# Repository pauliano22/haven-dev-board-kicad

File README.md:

# Haven Dev Board — KiCad Port

> **Current status (as of this commit): fabrication-ready.** Everything
> below this notice describes the *original* EasyEDA→KiCad port and was
> accurate when written, but predates the DRC/routing work that followed —
> it still says "no ERC or DRC has been run," which is no longer true. The
> board has since been rescaled to 73.1×161.1mm, fully routed (219 DRC
> violations remaining, all investigated and non-blocking; 2 cosmetic
> same-net internal BGA pairs unconnected), and DRC-verified via
> `kicad-cli`. See `FABRICATION_GUIDE.md` for current ordering instructions
> and `HAVEN_HARDWARE_REVIEW.md` for the full review trail. The rest of this
> file is kept as-is below for its record of the port's methodology and
> known limitations, most of which are still true (pin electrical types,
> unassigned pins, silkscreen fidelity, etc.) — only the DRC/routing status
> has changed.

A from-scratch KiCad recreation of the stock OpenEarable hardware (the base
Haven is built from), generated programmatically from the real EasyEDA Pro
project data rather than hand-traced from screenshots. This is **not** a
copy-paste of the user's live EasyEDA edits — it's a fresh port of the
*stock* OpenEarable design (`OpenEarable-PCB-main-2.0.epro`), per the
explicit scope agreed before this work started.

Open `kicad/haven_dev_board.kicad_pro` in KiCad. **No KiCad install or
`kicad-cli` was available in the sandbox this was built in — none of this
has been opened in real KiCad, run through ERC, or run through DRC.**
Treat the schematic as a strong first draft and the PCB as a best-effort
faithful port; both need a real review pass before anything is fabricated.
(Superseded — see the notice at the top of this file.)

## What's actually in here

| Section | Confidence | Why |
|---|---|---|
| BOM (89 parts, real values/part numbers) | High | Parsed directly from the `.epro`'s structured JSON, not guessed |
| Digital/power netlist (MCU, power management, flash, SD, USB, IO) | High | Two independent extraction methods agree exactly (see below) |
| Footprints (real pad shapes/sizes/positions) | High | Parsed directly from the real `.efoo` footprint data |
| PCB placement (component X/Y/rotation) | High | This is the **real board's actual placement**, not a guess |
| PCB routing (traces/vias/copper pours) | High for continuity, **unverified for DRC** | Real copper geometry ported directly; never run through a design-rule checker |
| Audio-analog section (ADAU1860 pins, mic, DAC) | Medium | Connectivity is real (same ground-truth source), but pin *electrical roles* (which precise decoupling network, differential pairing, etc.) haven't been cross-checked against the ADAU1860 datasheet |
| RF/antenna, USB signal integrity, any trace-width/impedance intent | **Needs real EE review** | Geometry ported as-is; nothing here was checked against RF/USB layout rules |
| Symbol/footprint graphics (visual appearance) | Cosmetic only | Pins are placed at electrically-correct coordinates but pin-stub direction and body-rectangle sizing are auto-generated, not hand-drawn — expect a plain, boxy look, not the polished look of a hand-drawn library part |

## Data source and methodology

The source is `OpenEarable-PCB-main-2.0.epro`, an EasyEDA Pro export. Unlike
the live `.eprj2` project file (an encrypted SQLite database), a `.epro` is
a zip of plaintext, line-delimited JSON records — genuinely parseable, not
reverse-engineered from pixels.

Two independent data sources were extracted and cross-checked against each
other:

1. **Schematic layer** (`.esch`, `.esym`): component placement, symbol pin
   layouts, and net-label text. EasyEDA's schematic format has no explicit
   netlist — connectivity has to be reconstructed from which pins sit near
   which net-label text. This reconstruction (`extracted/parse_netlist2.py`)
   hit two real bugs before it produced a trustworthy result, both fixed
   and documented in code comments:
   - A naive `name.split(".")[0]` truncated decimal component values
     (e.g. `"2.2uH.1"` → `"2"` instead of `"2.2uH"`), breaking symbol
     lookup for 15 parts. Fixed with a regex that strips only the trailing
     `.N` variant suffix, plus an HTML-entity unescape (BOM value strings
     use a literal `>`, symbol titles use `&gt;`).
   - The nRF5340 module's dedicated DC-DC/decoupling pins (`DECR`, `DCC`,
     `DECD`, `DCCD`, `DCCH` — per the module's own symbol pin names) were
     being swept into unrelated neighboring nets by the proximity-matching
     heuristic, since these pins sit only ~10 units from adjacent signal
     pins on a tight-pitch module. These pins are excluded from proximity
     matching entirely; per the nRF5340 datasheet they only ever connect
     to a local decoupling capacitor, never a routed signal net.

2. **PCB layer** (`.epcb`) — discovered partway through this work, and a
   materially better source: every real pad on the actual manufactured
   board has a `PAD_NET` record giving its **already-resolved** net name
   directly, plus a `COMPONENT` record giving its **real placed position
   and rotation** on the actual board. This is ground truth, not a
   reconstruction. **This is the netlist actually used in the generated
   schematic and PCB** (`extracted/pcb_netlist.json`,
   `extracted/pcb_placement.json`) — it covers ~85% of all pins vs. ~64%
   for the schematic-proximity heuristic, and every net checked against
   both sources agreed exactly (DIN, DOUT, BCLK, LRCLK, FLASH_RESET,
   SD_ENABLE, SCL1/SDA1, and the full GND net all matched).

   The PCB layer also contains real routed copper — 1003 trace segments,
   260 vias, and 6 ground/power copper pours — on a genuine 6-layer
   stackup (confirmed via `LAYER_PHYS` dielectric/copper-thickness
   records): `TOP / prepreg / GND-plane / core / Inner1 / prepreg /
   Inner2 / core / POWER-plane / prepreg / BOTTOM`. All of this routing
   was ported directly rather than re-routed from scratch.

Coordinate systems were independently reverse-engineered and validated for
each domain (schematic-space units are 10 mil per raw grid unit;
PCB-space units are 1 mil per raw unit — confirmed against overall board
span, ~13.5mm × 26.7mm, plausible for a small in-ear wearable). PCB-space
rotation was independently validated against real trace/via endpoints on
two components with 90°/270° rotations (not just 180°, which can't
distinguish rotation direction) — computed pad positions landed within
0.01 raw units (~0.0003mm) of real trace endpoints, confirming standard
CCW rotation with **no mirroring needed**, even for back-side (layer 2)
parts.

The board outline's arc segments (`POLY` records on the OUTLINE layer) use
a `(start, end, sweep-angle)` encoding with no explicit center point. The
center/midpoint formula was derived from scratch and verified in closed
form against two real corner-fillet arcs before being trusted for the
whole outline.

### Coordinate-generation strategy (why the connectivity should be trusted even without ERC)

Every generated symbol instance (schematic) and footprint instance (PCB)
is placed at **rotation zero**, with the component's real rotation baked
directly into each pin/pad's own local coordinate instead. This sidesteps
any uncertainty about whether KiCad's internal rotation transform sign
convention matches EasyEDA's: since only pure translation is asked of
KiCad, and the label/pad-net coordinates are computed with the exact same
Python expression used to place the pin/pad itself, they are numerically
identical by construction — not just "close." The actual rotation-direction
question was still independently resolved and validated (see above); this
strategy just removes it as a second, compounding source of risk.

## Known limitations / simplifications

- ~~**No ERC or DRC has been run.**~~ Superseded — see the notice at the
  top of this file. DRC has since been run extensively via `kicad-cli`
  (219 violations remaining, all investigated; see
  `HAVEN_HARDWARE_REVIEW.md`).
- **POLY-shaped pads** (rare — a few connector pads on J1/CN1 use a custom
  polygon rather than a rectangle/ellipse) are approximated by their
  bounding rectangle, not their exact polygon outline.
- **Via layer spans**: the source data's per-via layer-span field was
  empty for every via found, which is consistent with (but doesn't
  strictly prove) all-through vias. Every via is generated as a full
  F.Cu–B.Cu through via. If any are actually blind/buried, this needs
  correcting.
- **Board stackup thicknesses** are not precisely declared in the
  generated file (KiCad's default 1.6mm/2-layer-style general thickness
  is used) — the *layer names and count* (6 copper layers) are real and
  correct, but exact dielectric thicknesses from the source data were not
  carried through.
- **Silkscreen art, logos, and precise designator label placement** from
  the original board were not ported — only functional copper, pads, and
  the board edge. Reference designators use KiCad's default auto-placed
  text.
- **Pin electrical types** (input/output/power/etc.) are uniformly set to
  "passive" in the generated symbols. This was a deliberate choice: I
  don't have verified per-pin electrical-role data from any datasheet, and
  marking pins with specific types I can't back up would be fabricating
  detail I don't actually have grounds for. This means ERC in KiCad won't
  be meaningful for pin-direction conflicts until someone fills in real
  electrical types from actual datasheets.
- **~15% of pins have no assigned net** (72 of 460 PCB pads; a very
  similar fraction on the schematic side). Spot-checked and these are
  overwhelmingly genuine — reserved MCU pins (the DC-DC pins above),
  unused GPIOs, and connector pins with more physical positions than the
  design actually uses (e.g. CN1 pins 13–24, CARD1 pin 1). They are not
  silently dropped; they're just left unconnected in the generated files
  rather than fabricating a connection.

## A genuine anomaly in the *original* stock design — now resolved

One net in the real board data was literally named `#ERROR` by EasyEDA
itself (confirmed present in `extracted/netlist.json`'s raw source, not
introduced during this port) — it tied together MDBT531 pin 3 (`P1.08`,
a GPIO), Q2 pin 1 (a small MOSFET, `CSD13380F3T`), and U8 pin 1 (a 1MΩ
0201 resistor, despite the "U" designator). EasyEDA just never resolved
a human-readable name for this net.

Traced further and renamed to **`LED_ENABLE`**: R4 (510Ω) and U4 (a real
0201 LED, `XL-0201SURC`, per `HAVEN_BOM.csv`) are also on this net —
3V3 → U4 (LED) → R4 (current-limit) → Q2 (low-side switch to GND), gated
by U8 (1MΩ pulldown, default-off) and driven directly by MDBT531 P1.08.
A straightforward GPIO-controlled indicator LED. Pure rename in both the
schematic and PCB — zero electrical change, verified via DRC diff. The
net also had a genuine small routing gap (Q2's gate pad wasn't
connected to the rest of the net); that's now routed too.

## File layout

```
kicad/
  haven_dev_board.kicad_pro     project file
  haven_dev_board.kicad_sch     schematic (89 components, net labels for connectivity)
  haven_dev_board.kicad_sym     project symbol library (one symbol per component, no sharing)
  haven_dev_board.kicad_pcb     PCB (real placement, real footprints, real routing, real outline)
  footprints.pretty/            33 generated footprints
  sym-lib-table, fp-lib-table   project-local library tables

extracted/                      all extraction/generation scripts + intermediate JSON,
                                 kept for provenance and so the pipeline can be re-run
                                 (e.g. after a schematic re-export) rather than redone by hand
```

## Suggested next steps for a human pass

1. ~~Open in KiCad, run ERC and DRC, see what falls out.~~ Done — see the
   notice at the top of this file and `HAVEN_HARDWARE_REVIEW.md`.
2. Cross-check the ADAU1860 audio-analog section (U15's ~29 unmatched
   pins, mostly clustered here) against the real datasheet.
3. Review U2 (BQ25120A charger) and U6 (BQ27220 fuel gauge) — both have a
   meaningful number of unmatched pins too.
4. ~~Decide whether the `#ERROR` net circuit needs a real name/investigation.~~ Done — see above, now `LED_ENABLE`.
5. If this is meant to diverge from stock OpenEarable (per the earlier
   Gemini-assisted cleanup pass on the user's live EasyEDA project), diff
   this port against that pass and carry over the same changes here.

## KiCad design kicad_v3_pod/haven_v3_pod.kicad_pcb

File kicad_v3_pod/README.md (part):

# Haven v3 slim pod: schematic (2026-11-11)

**Decision (Paul, 2026-11-11):** build concept A of `DESIGN_BRIEF_SHELL_V3.md` with the microphone on the pod.
The in-ear piece becomes a small speaker on two wires, with no circuit board.

**Generated** by `tools/gen_v3_pod_schematic.py` from the v2 pod part list. Edit the script, not the `.kicad_sch`.

## Status
- 67 parts, 43 nets (v2 pod: 79 parts). `kicad-cli sch erc --severity-all`: **0 violations**.
- **Decision (Paul, 2026-11-11): 17 mm cell** (about 40 mAh; about 13 h quiet / 6 h loud by datasheet estimate). The first
  attempt with a 22 mm cell fitted only 50 of 67 parts on one face (`placement_attempt_2026-11-11.png`); the shorter cell
  frees the bottom face between y = +3.5 mm and the antenna keep-out for the test pads, charge pads, cell pads and the 32 kHz crystal.
- **Board: all 67 parts placed, routing NOT finished.** `haven_v3_pod.kicad_pcb` after `tools/gen_v3_pod_pcb.py`,
  `tools/route_v3_pod_pcb.py 40` (Freerouting), then `fix_v2_pod_pcb.py` and `route_rest_v2_pod.py` run with
  `HAVEN_PCB` / `HAVEN_WORK` pointing at v3.
  - Attempt 1 (audio chip at the right edge): 12 unconnected, 7 copper-to-edge, 11 dangling vias; capacitors up to 10 mm from
    their pins. Saved as `~/.cache/haven_builds/v3_pod_pcb/after_route_rest.kicad_pcb`.
  - Attempt 2 (audio chip moved to (1.2, -5.3), capacitors anchored on chip pins, worst about 6 mm): **16 unconnected,
    5 copper-to-edge, 15 dangling vias. This is the file in the repo.** Six of the failures are audio-chip balls whose
    fan-out via is boxed in at once (BCLK, PDMDIN, SDA1, SHPHLD, XO_R, XTALO): they need `rip_reroute_v2_pod.py` per net
    or hand-placed escapes, as v2 did.
  - Attempt 3 (20 mm cell, no 32 kHz crystal, 64 parts): **16 unconnected, 5 copper-to-edge, 18 dangling vias. This is the
    file in the repo now** (also `~/.cache/haven_builds/v3_pod_pcb/after_route_rest3.kicad_pcb`). Open: BCLK, LED_EN, PDMDIN,
    SCL1, SDA1 (2), SENSORS_ENABLE, SHIP_EN, SHPHLD, SPK+ (2), V_LS (2), XTALI (2), XTALO. Three attempts have all ended at
    12-16 open, mostly audio-chip balls boxed in at the chip. More autorouter passes will not fix this; it needs
    hand-planned escapes for the audio chip (which ball leaves on which layer), then the autorouter for the rest.
  - Attempt 4 (hand-planned, locked escapes for the audio chip in `gen_v3_pod_pcb.py`: `U15_ESCAPES`, five balls without
    vias, V_LS pour on In4 under the chip): **13 unconnected, 0 copper-to-edge, 8 dangling vias, 8 dangling tracks.
    This is the file in the repo now** (`after_route_rest4.kicad_pcb`). The stranded audio-chip signals (PDMDIN, SDA1,
    SCL1, XTALI, LRCLK) are now routed. Still open: BCLK, SHIP_EN, SENSORS_ENABLE (long runs to the module), SHPHLD to its
    test pad, SPK- to its wire pad, XTALO and XO_R (the crystal sits left of the chip while its signals leave from the
    top and its resistor is on the right: move CRYSTAL1 and R28 to the top-right of U15), and five V_LS fragments
    (enlarge the V_LS pour or give the capacitors vias into it).
  - 2026-11-12, what the layer pictures showed: In2 and In3 are nearly empty on the attempt-4 board. The open
    connections are not a lack of room overall. Their end points are boxed in on the top face (parts 0.15 mm apart leave
    no gap a 0.09 mm track can pass with 0.1 mm clearance, and a via in the pad is too close to neighbouring tracks).
    Tools added: `multilayer_route.HEUR_W` (greedier search, env `HAVEN_HEUR_W=2.0`, makes long routes findable) and
    `tools/route_islands_v3_pod.py` (tries every pad, via and track end of the two disconnected pieces, then a
    via-in-pad). On the attempt-4 board they closed 2 more (11 open); the rest needed a placement change.
  - Attempt 5 (2026-11-12): CRYSTAL1 moved above the audio chip's top-right corner (`HAVEN_XTAL`, default 2.6,-2.85),
    a filled via in every V_LS pad before routing, V_LS pour on In4 enlarged to cover all of them (it now replaces
    ground on In4 below the module; In1 stays solid ground). 64 of 64 placed, no shorts or clearance errors before
    routing. Known cost: D1 (charge-pad ESD diode) landed 15 mm from its pad.
    **Result, 2026-11-13: 3 signals open (DOUT at the audio chip's B1 ball, CHG_ERR at the power chip's E3 ball,
    LED_EN at the module's pad 34), plus one ground-fill island on the top face at the bottom-left corner. No
    clearance, short or hole errors. 3 "connection too narrow" pour necks, 10 dangling stubs, 4 dangling vias to tidy.
    This is the file in the repo** (copy: `~/.cache/haven_builds/v3_pod_pcb/attempt5_final_3open.kicad_pcb`).
    How it got there: Freerouting left 37 open; `fix` + `route_rest` got to 13; `route_islands` 11; `rip_reroute` 7;
    hand-planned In2 exits for the power chip's inner balls D3/D4 through E3/E4 closed SHIP_EN and SHPHLD; a hand-placed
    0.15/0.25 via closed the SDA1 pull-up; CHG_STAT, ICHG, VBAT re-routed around them.
  - Why the last three are stuck (seen in zoomed layer pictures, `zoom.py` / `viamap.py` in the cache folder):
    - DOUT: ball B1 has no via (BCLK's In2 exit passes under it). On the top face it is in a pocket closed by the SPK-
      track (x = 98.92), the C33 pad above and the DIN track below; every via spot in the pocket is taken on In2-In4.
    - CHG_ERR: ball E3 has no via (SHPHLD's In2 exit passes under it). The 0.6 mm channel between the chip's bottom row
      and C112 is closed at both ends and has tracks under it on every layer.
    - LED_EN: long run from the module's inner pad; not looked at closely yet.
  - Lessons for the generator before any attempt 6:
    1. A via in every V_LS pad plus the fix script's ground vias makes a wall of through-vias around the audio chip on
       all layers. Put vias only in the 10 uF pads and let small capacitors share them on the top face.
    2. The hand-planned exits end stacked at the same x/y on different layers (G5: In2, In3 and B; B1/C1: top and
       In2), so no via can be placed at any stub end. Fan the ends apart by at least 0.3 mm.
    3. Keep a 0.8 mm part-free strip below the power chip (as already done left of the audio chip) and plan D3/D4 exits
       in the generator (`U2` balls E3/E4 without vias, as patched by hand here).
    4. CHG_ERR is not used by firmware. Leaving it unconnected is an option (the nPM1100 pin is an open-drain output)
       but it removes charger-fault reporting; not done, Paul's call.
  - **2026-11-13, later: ALL CONNECTIONS ROUTED.** `kicad-cli pcb drc --schematic-parity`: 0 unconnected, 0 errors,
    0 schematic parity issues, 2 warnings (dead-end stubs on SCL1 and XTALO that are part of in-use tracks). Mirror
    check passes on all five chips. 1909 track segments, 185 vias (132 are the 0.15/0.25 filled size). Snapshot:
    `~/.cache/haven_builds/v3_pod_pcb/v3_pod_ROUTED_CLEAN_2026-11-13.kicad_pcb`. This is the file in the repo.
    - Attempt 6 (generator with the lessons below) was NOT better: 6 open + 22 copper-to-edge errors after the same
      stages. Snapshot `attempt6_final_6open_22edge.kicad_pcb`. The repo board is attempt 5, finished by targeted fixes.
      **The generator in `tools/gen_v3_pod_pcb.py` now produces the attempt-6 placement, not the repo board. Do not
      regenerate over the routed board.** The routed board's placement is in `placed5_unrouted.kicad_pcb`.
    - How the last ones closed: LED_EN by a small via beside Q2 after moving an unfinished CHG_ERR track; DOUT's real
      blockage was at the module (pad 38 walled in by the SPARE_P1_13 track), fixed by pulling up SPK- and SPARE,
      routing DOUT end to end, then re-routing those two; C40's ground pad got its own via after re-routing an SDA1
      segment; CHG_ERR by pulling up SHIP_EN and CHG_STAT near the power chip, routing it first, then those two.
      Scripts used are in the cache folder (`dout_direct.py`, `chgerr.py`, `join_pours.py`, `prune.py`).
    - V_LS fill minimum width raised to 0.15 mm so nothing depends on a 0.05 mm neck; the audio chip's V_LS balls
      that relied on such necks got tracks.
  - **This is a board that passes the rule check, not a reviewed layout. Known weak spots to fix or accept before any order:**
    1. Every power track is the minimum 0.09 mm (VBAT 24 mm, VSYS 19 mm, +1V8 44 mm, V_LS 31 mm, VBUS 30 mm, SW 6 mm,
       SPK+/SPK- 18 mm each). Resistance is tolerable at these currents on paper (about 0.13-0.5 ohm per rail), but
       the buck's SW node and input loop should be short and wide. Needs a widening pass; the fix script widened none.
    2. Audio-chip supply balls D1/E1 reach V_LS through a 6 mm long 0.09 mm track. Should be short and wide.
    3. Decoupling capacitors are up to 6-8 mm from the pins they serve; the charge-pad ESD diode D1 is 15 mm from its pad.
    4. Buck layout (U2, L2, C110-C114) has not been compared with Nordic's reference layout.
    5. Crystal tracks (XTALI/XTALO/XO_R) route length and what runs beside them not reviewed.
    6. Cell tolerances, spring-pin land pattern on P1/P2 (decision 2026-11-13), U3 handedness by convention only.
  - **2026-11-13, widening and review pass:**
    - `tools/widen_v3_pod.py` widened power and speaker segments wherever 0.1 mm clearance allowed, no new rule
      errors. Share of length widened / average width: +1V8 75 % / 0.19 mm, SW 77 % / 0.14, VSYS 58 % / 0.14,
      VBUS 25 % / 0.16, VBAT 16 % / 0.16, V_LS 51 % / 0.13, SPK+ 69 % / 0.15, SPK- 83 % / 0.17, DVDD 49 % / 0.13.
      The parts that stayed 0.09 mm are under and between the chips.
    - Measured on the board (straight-line distances):
      - Audio chip: every V_LS ball has a 10 uF within 0.9-2.0 mm. DVDD's capacitors are 3.2-3.5 mm away. CM 1.7 mm.
      - Power chip: VBUS 1.5 mm, VSYS 1.8-2.1 mm, VBAT 2.3-2.5 mm, +1V8 1.7 mm, DEC 1.8 mm. Acceptable for a prototype.
      - **Buck switching node: 5.7 mm of track with 2 vias through the bottom layer; the inductor is 4.5 mm from
        the SW ball.** Nordic's reference keeps it adjacent. Expect more radiated noise and ripple; measure.
      - **Radio module supply: Raytac's reference circuit (spec section 8.1.1, read as an image) shows 4.7 uF on VDD.
        Ours (C101) is 12 mm from the VDD pads 26/29; the nearest capacitor of any kind is 10 mm away.** Cause: the
        placer was told not to anchor parts on the module. No free spot for an 0402 within 2 mm was found on the
        routed board. Fix in the next layout pass (move W5/W6 down about 0.6 mm and fit a capacitor between them and
        the module), or accept for the first boards and check the module's supply ripple on the bench.
      - Crystal: XTALI 5.0 mm / 3 vias, XTALO 7.2 mm / 2 vias, XO_R 5.4 mm. Long for a crystal; adds roughly 1 pF
        per node (estimate). Start-up and frequency to be checked on the bench.
      - I2C runs are 18-20 mm; fine at 400 kHz with the 2 kohm pull-ups.
    - Factory files exported: `fab/v3_pod/` (gerbers zip, BOM, placement file; `tools/export_v2_fab.py v3pod`).
      BOM: every part has a JLCPCB/LCSC number except the radio module (blank on purpose, as on v2). Added
      L2 = C337891 (Murata DFE201610E-2R2M=P2) and R111 = C138153 (Yageo RC0201FR-0730KL), from LCSC listings via search.
      **Not yet done: JLCPCB quote and their DFM check, placement-preview rotation check, 13 hand-soldered pads
      (wires, test pads, charge pads) are not in the placement file by design.**
    - Final state: 0 unconnected, 0 errors, 0 parity issues, 2 warnings. Snapshot `v3_pod_FINAL_2026-11-13.kicad_pcb`.
  - **2026-11-13, the two review fixes (Paul: "go ahead and fix those two"):**
    - Module supply: new **C117, 1 uF 0201** (same part as the other 1 uF, LCSC C76929), in the 0.9 mm strip right of
      the module at (104.35, 97.55), 1.1 mm from VDD pad 29, ground via in its pad. It is 0.29 mm from the module's
      body edge and 0.29 mm from the board edge: tight for assembly, check JLCPCB's DFM. C101 (4.7 uF) stays where it
      is as bulk. This is NOT Raytac's 4.7 uF at the pin: no stocked 0201 4.7 uF was confirmed (Samsung
      CL03A475MQ3CRNC exists but no LCSC number found) and nothing larger fits. 65 parts now.
    - Buck: L2 turned 180 degrees so its SW pad faces the chip; SW re-routed. **SW: 5.7 mm -> 4.4 mm, still 2 vias
      (the one in ball A4 plus one at the inductor), widths up to 0.3 mm, 72 % of it widened.** Inductor SW pad is
      3.8 mm from ball A4; its output pad is 4.9 mm from the output capacitor C114. A modest gain. Putting the
      inductor and C114 next to the chip as in Nordic's reference means re-placing the whole power corner (about 12
      parts) and re-routing it: not done. Measure +1V8 ripple and audio noise on the first boards.
    - After both: 0 unconnected, 0 errors, 0 parity issues, 2 warnings; mirror check passes; fab files re-exported
      (52 placements). Snapshot `v3_pod_FINAL2_2026-11-13.kicad_pcb`.
  - **2026-11-14: spring-pin lands and power corner re-laid (Paul: "do everything you can without me").**
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
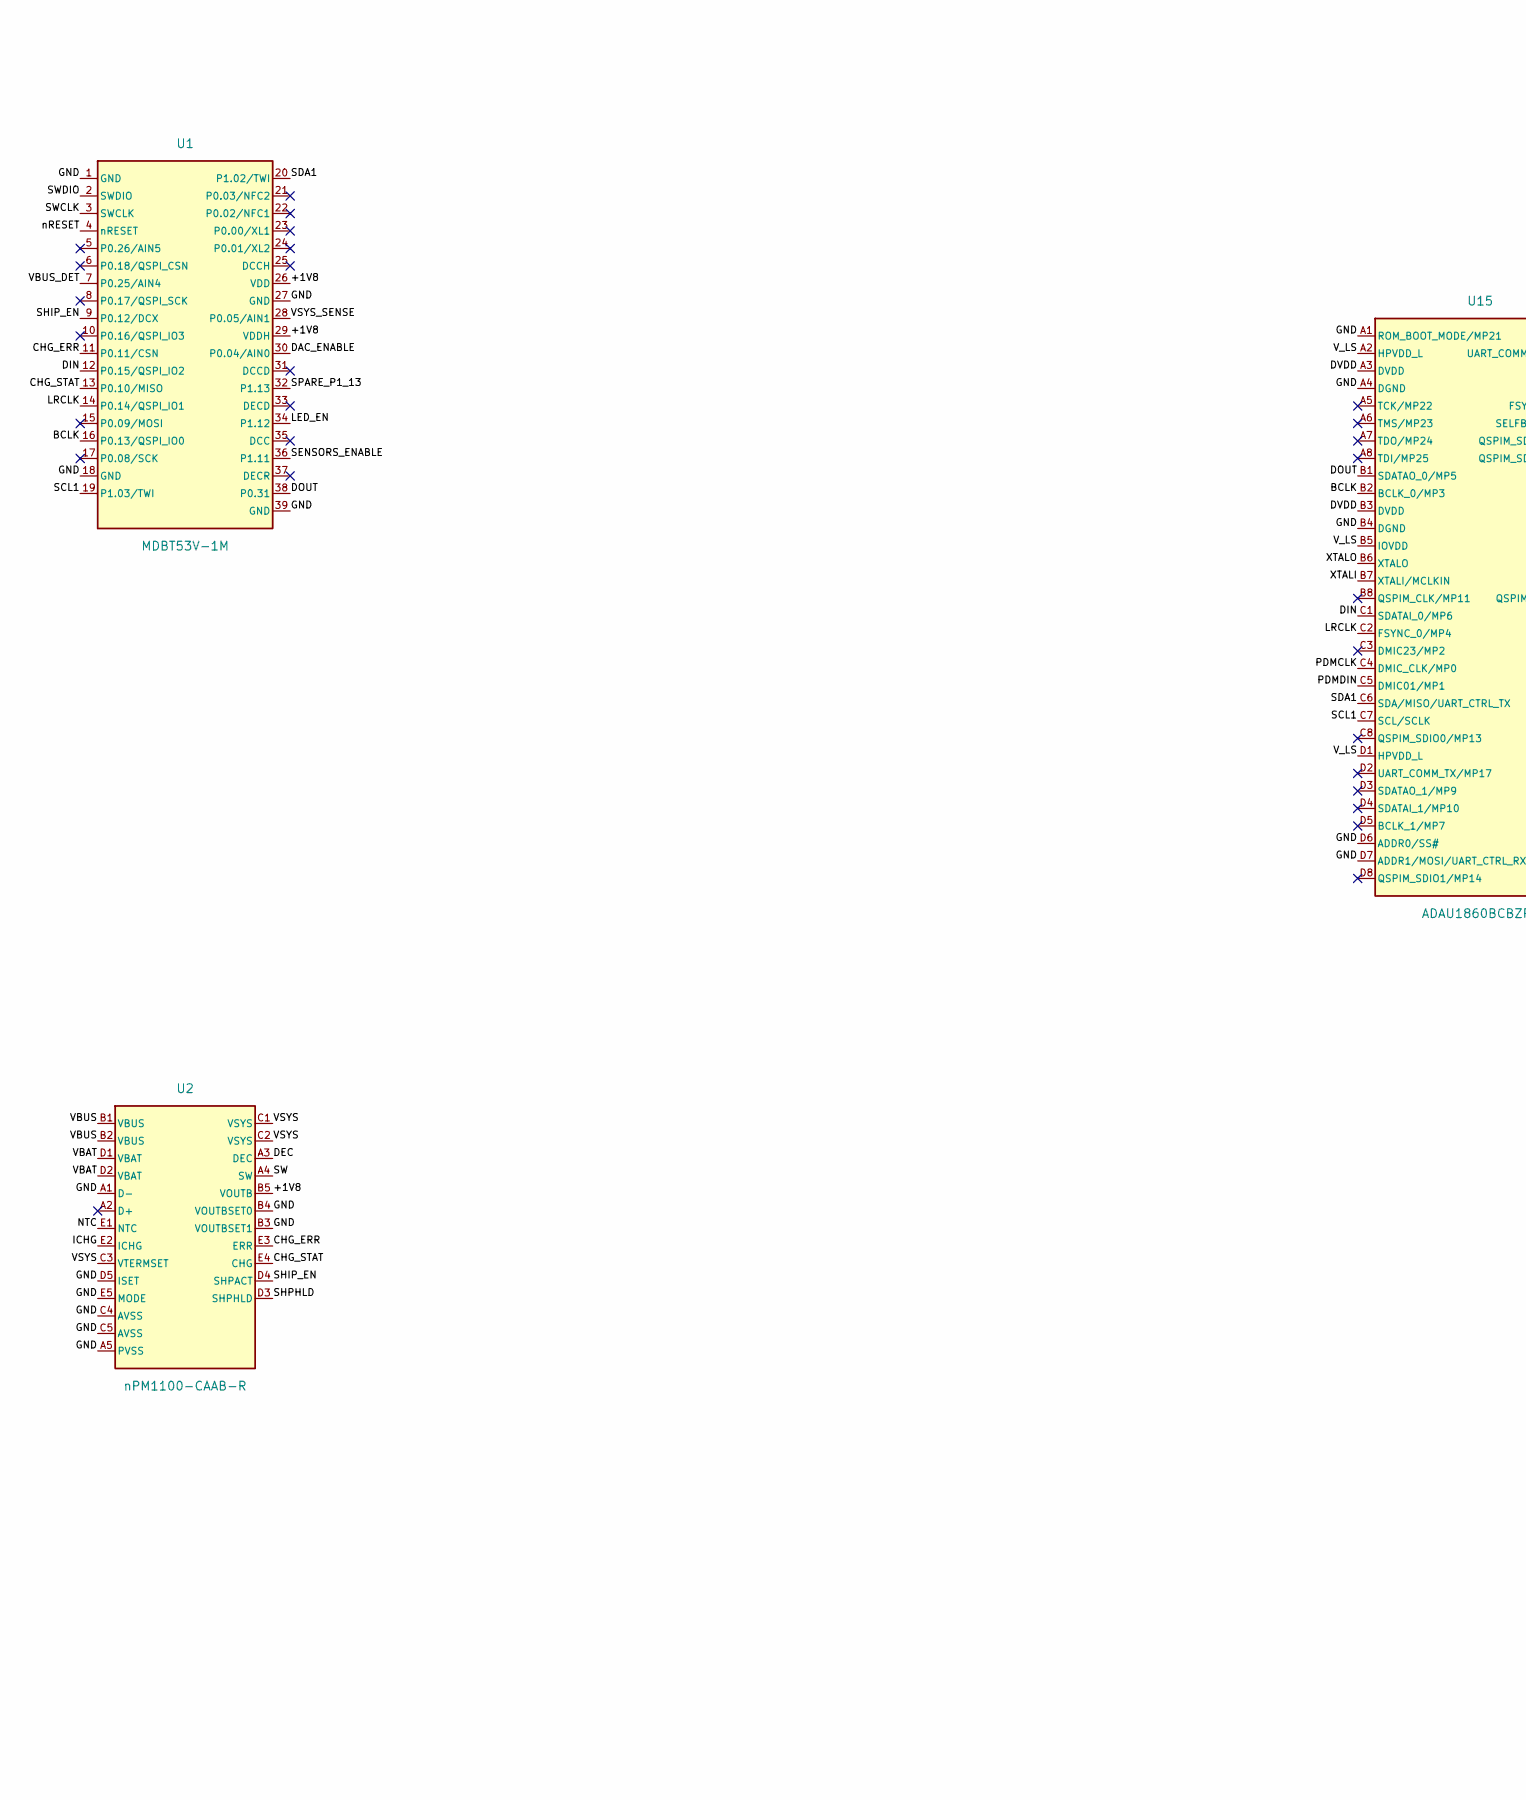
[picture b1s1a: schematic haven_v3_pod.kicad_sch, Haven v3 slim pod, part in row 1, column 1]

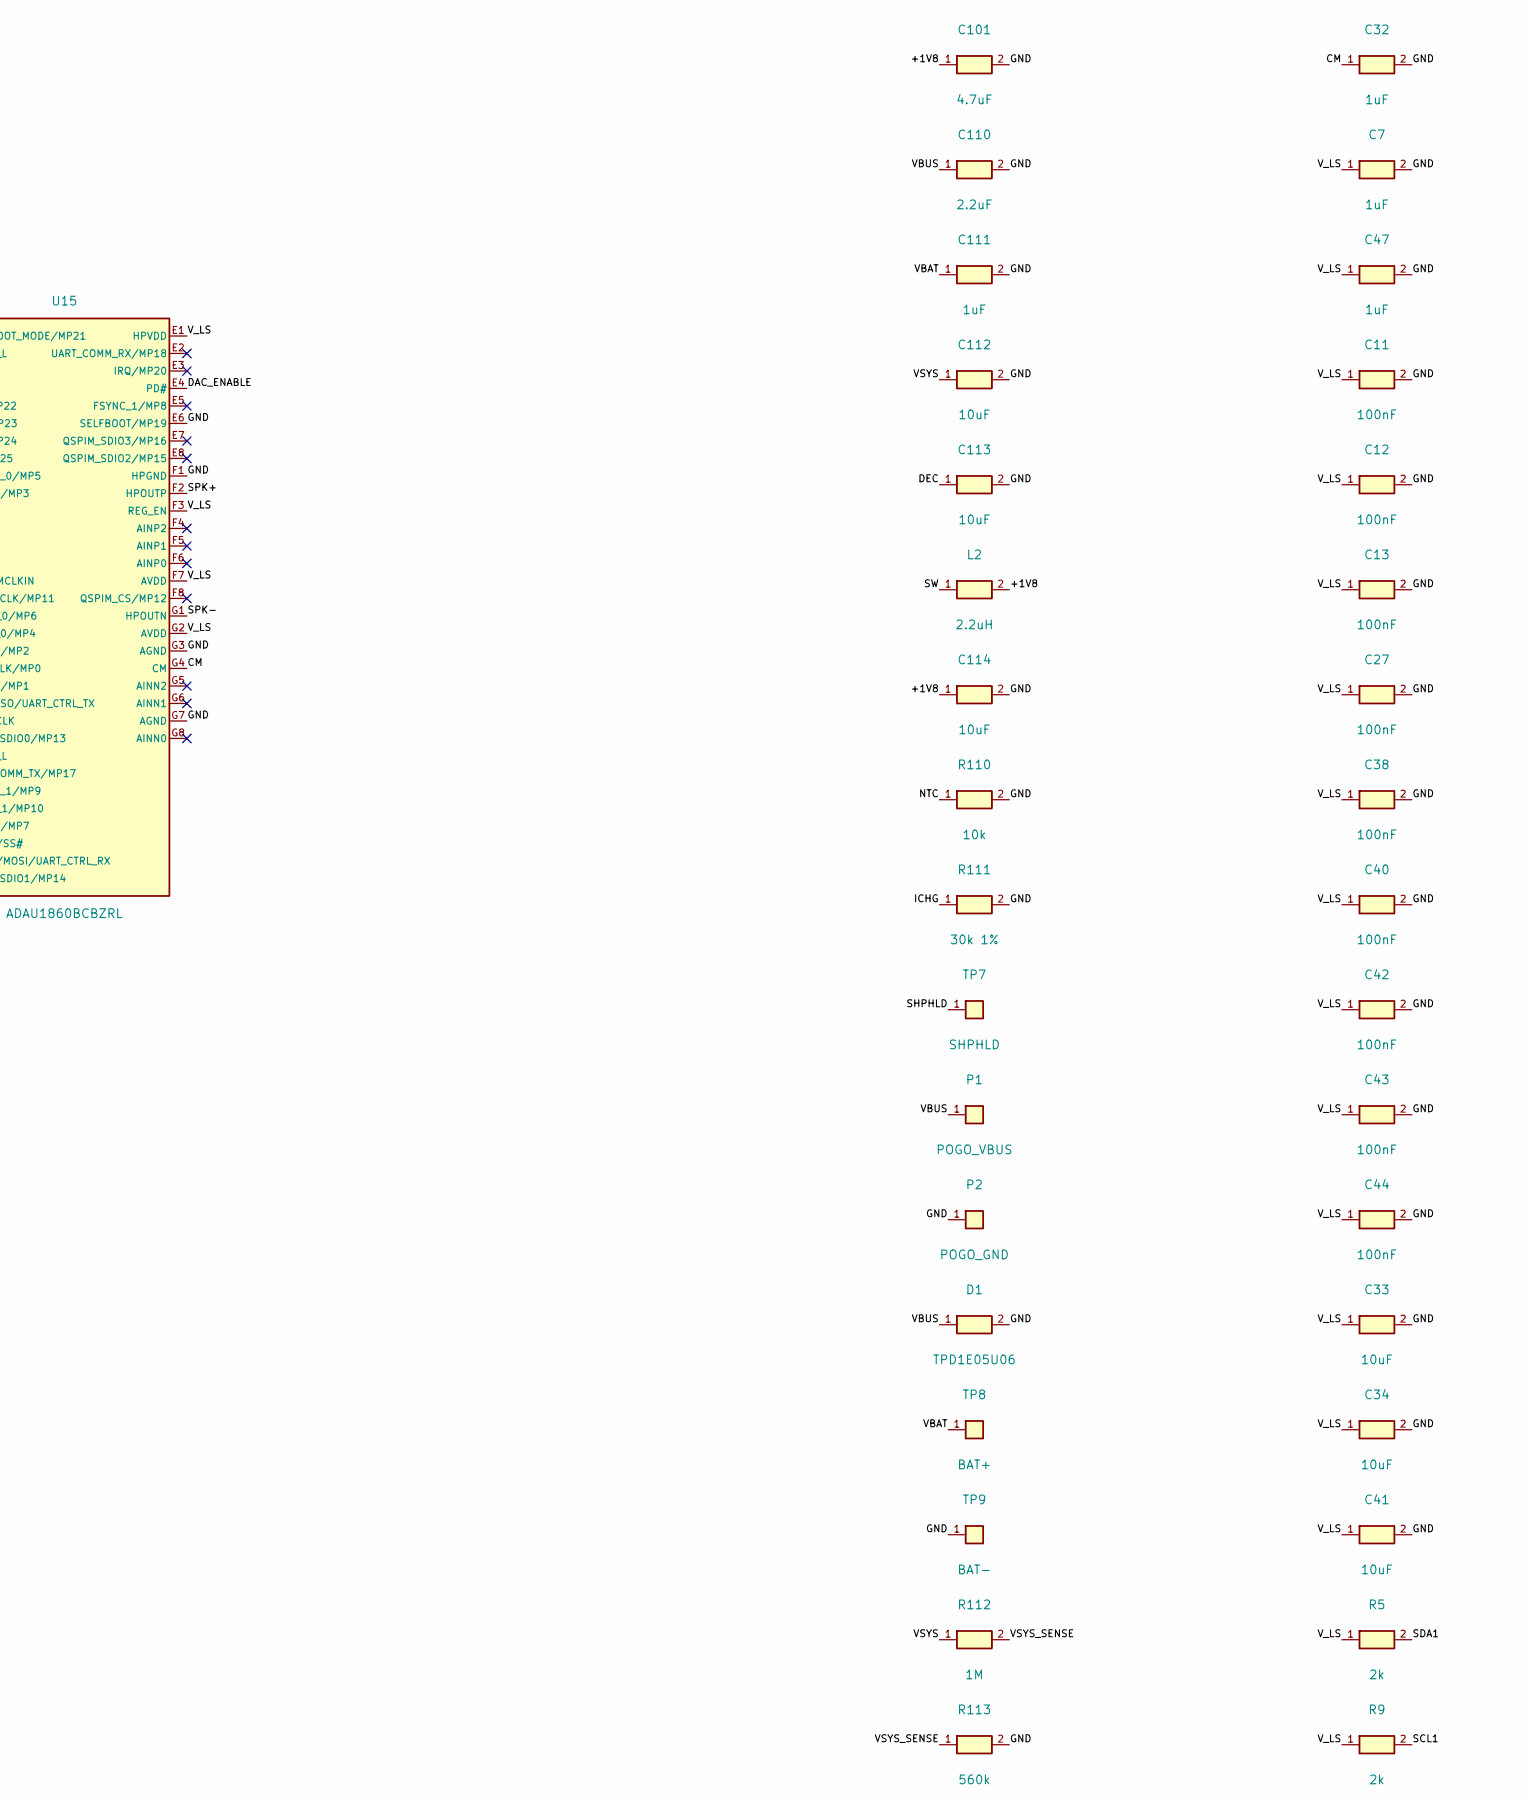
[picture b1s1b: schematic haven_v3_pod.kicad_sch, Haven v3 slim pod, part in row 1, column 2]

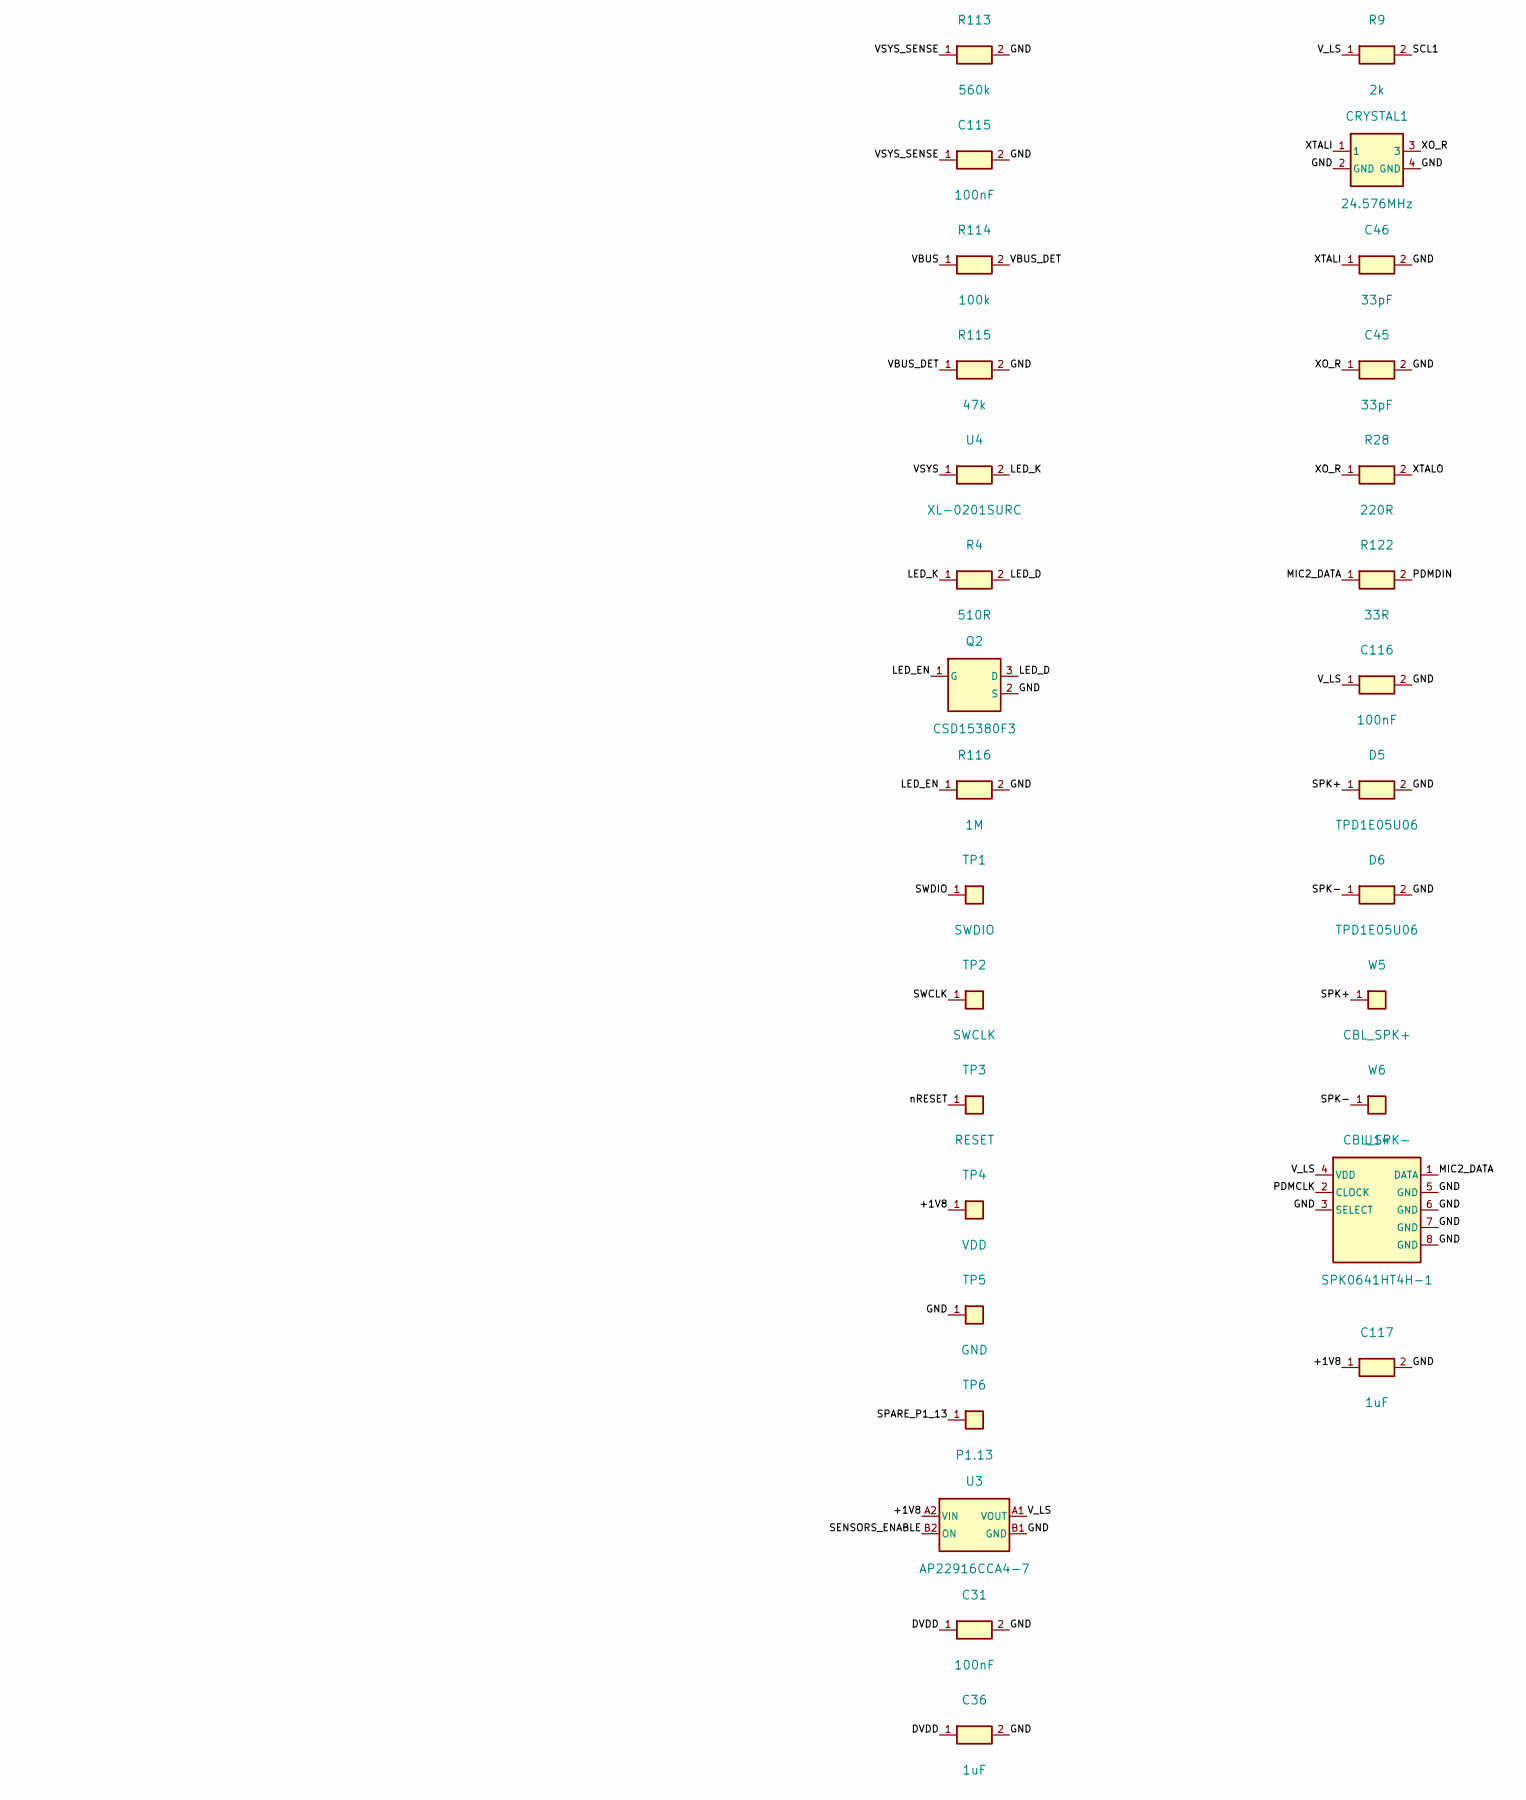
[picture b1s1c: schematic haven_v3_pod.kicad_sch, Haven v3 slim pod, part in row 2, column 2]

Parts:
C7, C32, C36, C47, C111, C117: 1uF; C0201; MPN GRM033R60J105KEA2D; LCSC C76929
C11, C12, C13, C27, C31, C38, C40, C42, C43, C44, C115, C116: 100nF; C0201; MPN GRM033R60J104KE19D; LCSC C76928
C33, C34, C41, C112, C113, C114: 10uF; C0402; MPN CL05A106MQ5NUNC; LCSC C15525
C45, C46: 33pF; C0201; MPN GRM0335C1H330JA01D; LCSC C76925
C101: 4.7uF; C0402; MPN CL05A475KP5NRNC; LCSC C368809
C110: 2.2uF; C0402; MPN CL05A225KA5NUNC; LCSC C307418
CRYSTAL1: 24.576MHz; CRYSTAL-SMD_4P-L2.0-W1.6-BL_HUAXIN_CN4; MPN CN4024M57620001; LCSC C7294677
D1, D5, D6: TPD1E05U06; D_SOD-523; MPN TPD1E05U06DYAR; LCSC C3702980
L2: 2.2uH; L_2016; MPN DFE201610E-2R2M=P2; LCSC C337891
P1: POGO_VBUS; SpringPin_2.0
P2: POGO_GND; SpringPin_2.0
Q2: CSD15380F3; PICOSTAR-3_L0.7-W0.6-P0.40-TL; MPN CSD15380F3; LCSC C529568
R4: 510R; R0201; MPN WR02X511JAL; LCSC C180335
R5, R9: 2k; R0201; MPN CR0201JH0202G; LCSC C100158
R28: 220R; R0201; MPN RC0201FR-07220RL; LCSC C274342
R110: 10k; R0201; MPN RC0201FR-0710KL; LCSC C106225
R111: 30k 1%; R0201; MPN RC0201FR-0730KL; LCSC C138153
R112, R116: 1M; R0201; MPN CQ01WMJ0105TEE; LCSC C5151554
R113: 560k; R0201; MPN RC0201FR-07560KL; LCSC C295807
R114: 100k; R0201; MPN RC0201FR-07100KL; LCSC C106224
R115: 47k; R0201; MPN RC0201FR-0747KL; LCSC C138139
R122: 33R; R0201; MPN ERJ1GNF33R0C; LCSC C717007
TP1: SWDIO; TestPad_0.8
TP2: SWCLK; TestPad_0.8
TP3: RESET; TestPad_0.6
TP4: VDD; TestPad_0.8
TP5: GND; TestPad_0.6
TP6: P1.13; TestPad_0.8
TP7: SHPHLD; TestPad_0.8
TP8: BAT+; Pad_1.2
TP9: BAT-; Pad_1.2
U1: MDBT53V-1M; MPN MDBT53V-1M
U2: nPM1100-CAAB-R; WLCSP-25_2.075x2.075_P0.4; MPN NPM1100-CAAB-R; LCSC C7016010
U3: AP22916CCA4-7; X1-WLB0808-4_L0.8-W0.8-P0.40-TL; MPN AP22916CCA4-7; LCSC C3246319
U4: XL-0201SURC; LED-SMD_L0.65-W0.35-P0.41_XL-0201SURC; MPN XL-0201SURC; LCSC C3646923
U14: SPK0641HT4H-1; MIC_SPK0641HT4H-1; MPN SPK0641HT4H-1; LCSC C5159510
U15: ADAU1860BCBZRL; BGA-56_L3.0-W2.7-P0.35-R8-C7-TL; MPN ADAU1860BCBZRL; LCSC C17592940
W5: CBL_SPK+; WirePad_0.8
W6: CBL_SPK-; WirePad_0.8

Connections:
/+1V8: C101.1, C114.1, C117.1, L2.2, TP4.1, U1.26 (VDD), U1.29 (VDDH), U2.B5 (VOUTB), U3.A2 (VIN)
/BCLK: U1.16 (P0.13/QSPI_IO0), U15.B2 (BCLK_0/MP3)
/CHG_ERR: U1.11 (P0.11/CSN), U2.E3 (ERR)
/CHG_STAT: U1.13 (P0.10/MISO), U2.E4 (CHG)
/CM: C32.1, U15.G4 (CM)
/DAC_ENABLE: U1.30 (P0.04/AIN0), U15.E4 (PD#)
/DEC: C113.1, U2.A3 (DEC)
/DIN: U1.12 (P0.15/QSPI_IO2), U15.C1 (SDATAI_0/MP6)
/DOUT: U1.38 (P0.31), U15.B1 (SDATAO_0/MP5)
/DVDD: C31.1, C36.1, U15.A3 (DVDD), U15.B3 (DVDD)
/GND: C7.2, C11.2, C12.2, C13.2, C27.2, C31.2, C32.2, C33.2, C34.2, C36.2, C38.2, C40.2, C41.2, C42.2, C43.2, C44.2, C45.2, C46.2, C47.2, C101.2, C110.2, C111.2, C112.2, C113.2, C114.2, C115.2, C116.2, C117.2, CRYSTAL1.2 (GND), CRYSTAL1.4 (GND), D1.2 (A), D5.2 (A), D6.2 (A), P2.1, Q2.2 (S), R110.2, R111.2, R113.2, R115.2, R116.2, TP5.1, TP9.1, U1.1 (GND), U1.18 (GND), U1.27 (GND), U1.39 (GND), U2.A1 (D-), U2.A5 (PVSS), U2.B3 (VOUTBSET1), U2.B4 (VOUTBSET0), U2.C4 (AVSS), U2.C5 (AVSS), U2.D5 (ISET), U2.E5 (MODE), U3.B1 (GND), U14.3 (SELECT), U14.5 (GND), U14.6 (GND), U14.7 (GND), U14.8 (GND), U15.A1 (ROM_BOOT_MODE/MP21), U15.A4 (DGND), U15.B4 (DGND), U15.D6 (ADDR0/SS#), U15.D7 (ADDR1/MOSI/UART_CTRL_RX), U15.E6 (SELFBOOT/MP19), U15.F1 (HPGND), U15.G3 (AGND), U15.G7 (AGND)
/ICHG: R111.1, U2.E2 (ICHG)
/LED_D: Q2.3 (D), R4.2
/LED_EN: Q2.1 (G), R116.1, U1.34 (P1.12)
/LRCLK: U1.14 (P0.14/QSPI_IO1), U15.C2 (FSYNC_0/MP4)
/MIC2_DATA: R122.1, U14.1 (DATA)
/NTC: R110.1, U2.E1 (NTC)
/PDMCLK: U14.2 (CLOCK), U15.C4 (DMIC_CLK/MP0)
/PDMDIN: R122.2, U15.C5 (DMIC01/MP1)
/SCL1: R9.2, U1.19 (P1.03/TWI), U15.C7 (SCL/SCLK)
/SDA1: R5.2, U1.20 (P1.02/TWI), U15.C6 (SDA/MISO/UART_CTRL_TX)
/SENSORS_ENABLE: U1.36 (P1.11), U3.B2 (ON)
/SHIP_EN: U1.9 (P0.12/DCX), U2.D4 (SHPACT)
/SHPHLD: TP7.1, U2.D3 (SHPHLD)
/SPARE_P1_13: TP6.1, U1.32 (P1.13)
/SPK+: D5.1 (K), U15.F2 (HPOUTP), W5.1
/SPK-: D6.1 (K), U15.G1 (HPOUTN), W6.1
/SW: L2.1, U2.A4 (SW)
/SWCLK: TP2.1, U1.3 (SWCLK)
/SWDIO: TP1.1, U1.2 (SWDIO)
/VBAT: C111.1, TP8.1, U2.D1 (VBAT), U2.D2 (VBAT)
/VBUS: C110.1, D1.1 (K), P1.1, R114.1, U2.B1 (VBUS), U2.B2 (VBUS)
/VBUS_DET: R114.2, R115.1, U1.7 (P0.25/AIN4)
/VSYS_SENSE: C115.1, R112.2, R113.1, U1.28 (P0.05/AIN1)
/V_LS: C7.1, C11.1, C12.1, C13.1, C27.1, C33.1, C34.1, C38.1, C40.1, C41.1, C42.1, C43.1, C44.1, C47.1, C116.1, R5.1, R9.1, U3.A1 (VOUT), U14.4 (VDD), U15.A2 (HPVDD_L), U15.B5 (IOVDD), U15.D1 (HPVDD_L), U15.E1 (HPVDD), U15.F3 (REG_EN), U15.F7 (AVDD), U15.G2 (AVDD)
/XO_R: C45.1, CRYSTAL1.3, R28.1
/XTALI: C46.1, CRYSTAL1.1, U15.B7 (XTALI/MCLKIN)
/XTALO: R28.2, U15.B6 (XTALO)
/nRESET: TP3.1, U1.4 (nRESET)

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
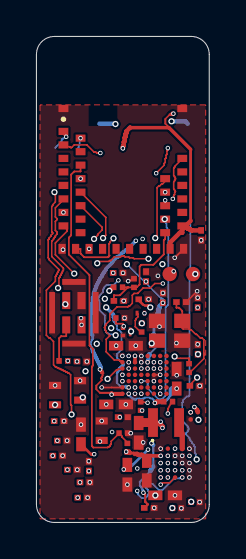
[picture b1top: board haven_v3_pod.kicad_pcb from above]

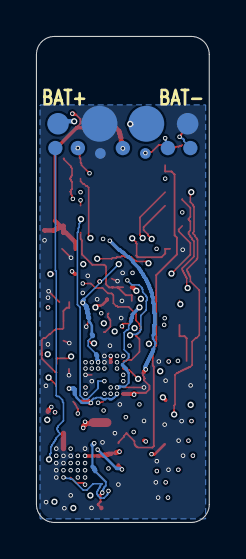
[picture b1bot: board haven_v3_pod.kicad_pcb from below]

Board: 6 copper layers, 9.6 x 27.0 mm, 65 parts (11 on the bottom side), 41 nets.

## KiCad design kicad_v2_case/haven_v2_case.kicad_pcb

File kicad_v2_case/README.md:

# Haven v2 BTE charging case: schematic

Generated by `tools/gen_v2_case_schematic.py` (edit the script, not the `.kicad_sch`).
Charge-only, no microcontroller. 26 parts, 11 nets. `kicad-cli sch erc`: 0 violations.

```
USB-C (5 V sink: CC1/CC2 5.1k) ── MCP73831 charger, 250 mA ── ~800 mAh 1S LiPo (with PCM), JST-SH
                                       └─ red LED: on while charging
LiPo ── TPS61023 boost, 4.95 V, always on ── pogo pins: L pod (VBUS, GND), R pod (VBUS, GND)
```

## Decisions
- **No IP5306.** It switches its 5 V output off below ~45 mA, and two charging pods (~40 mA
  each, falling as they fill) sit right at that edge.
- **No BQ25619.** Its 5 V boost needs an I2C write to enable, so it needs a microcontroller.
- **Charger:** MCP73831 (LCSC C424093). The TP4054 has the same pinout and the same
  ~1000/R(kΩ) mA rule, so it is a drop-in if MCP73831 stock is short. R3 = 4.02k gives ~250 mA.
- **Boost:** TI TPS61023 (LCSC C1852149), values from its datasheet (SLVSF14B, Figure 8-1):
  1 µH, 10 µF in, 2 × 22 µF out, 732k/100k → 4.95 V. EN is tied to VIN, so it is always on:
  20–30 µA standby, about 3 years on a full 800 mAh cell. A short on the pogo pins folds the
  output back to ~350 mA, and it restarts when the short is released (datasheet 7.3.7).
- **Per-pod current:** each pod's nPM1100 limits itself to 100 mA, so no per-pod switch.
- **Battery:** 800 mAh is about 3 full recharges of both pods (2 × ~100 mAh per recharge,
  ~85% boost efficiency, plus margin). Buy a cell **with** a protection board (PCM); the board has
  no undervoltage cut-off of its own.
- **Pogo pins:** 2 per pod, **5.0 mm apart**, centred on the pod's 3 mm magnet. They mate the two
  Ø1.5 mm contacts in the pod shell's bottom end (haven-hardware `v2_bte`, PAD_PITCH 2.5 mm), not
  the board pads directly: on the first build each shell contact is a short wire to P1/P2.
  The footprint is a 2.2 mm round seat for a 2.0 mm-base SMD spring pin; the actual part is open.
- ESD (TPD1E05U06, same as the pod) on USB VBUS and on the pogo VBUS rail.

## Layout (2026-11-05)
- 44 × 15.5 mm, 2 layers, 1.0 mm, all parts on top. Outline and pin positions come from
  haven-hardware `mechanical_cad/v2_bte/case.json` (the board sits on the case's bottom plate
  under the pods).
- `kicad-cli pcb drc --schematic-parity --severity-all`: **0 violations, 0 unconnected, 0 parity
  issues.** JLCPCB standard 2-layer rules (0.15 mm clearance, 0.6/0.3 mm vias).
- Flow: `tools/gen_v2_case_schematic.py` → `tools/gen_v2_case_pcb.py` (placement, the SW trace,
  pours) → `tools/route_v2_case_pcb.py` (Freerouting) → `tools/stitch_v2_case_pcb.py` (GND
  stitching). One GND island (under R2) got a via by hand after stitching.
- The spring pins sit exactly under the pod contacts. USB-C (J1) is at x = −2 mm with its mouth
  flush with the back edge, and the charge LED (D2) is at the back edge behind the case's light hole.
- Boost layout: U2's SW pin sits straight under L1's SW pad (0.35 mm trace, ~1.3 mm long). The
  output caps are on the side the VOUT pin faces, and the input cap is beside L1's VBAT pad.
- Spring pins: candidate Kinghelm KH-PG2011005-DZ (LCSC C2842935), SMD, 11 mm free, 2 mm base, on
  the 2.2 mm round seat. The case puts the board top 10.0 mm below the pod contacts (~1 mm of
  compression); the stroke isn't published, so measure a real pin and adjust `POGO_WORK_H` in
  haven-hardware `case.py`.

## Firmware impact
- Pods see 5 V on VBUS whenever they sit in the case (VBUS_DET). The pod firmware should drop to
  its lowest-power state there (no advertising), or it will drain the case battery.

## Open
1. Pogo pin: confirm KH-PG2011005-DZ's stroke and base land pattern on a real part.
2. (Done 2026-11-05: every placed part has a verified LCSC number.)

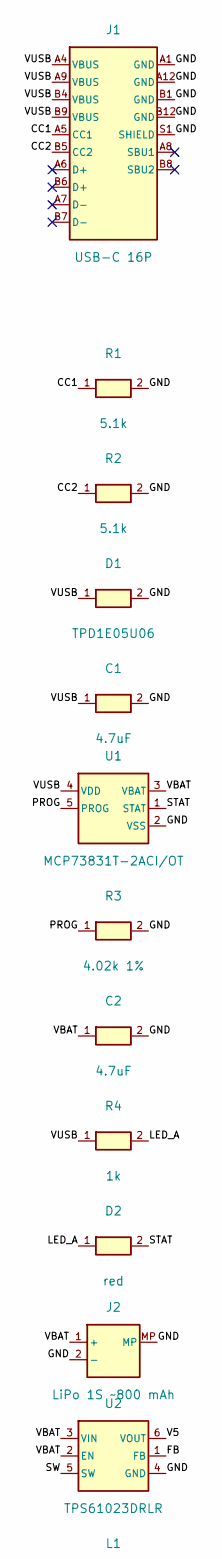
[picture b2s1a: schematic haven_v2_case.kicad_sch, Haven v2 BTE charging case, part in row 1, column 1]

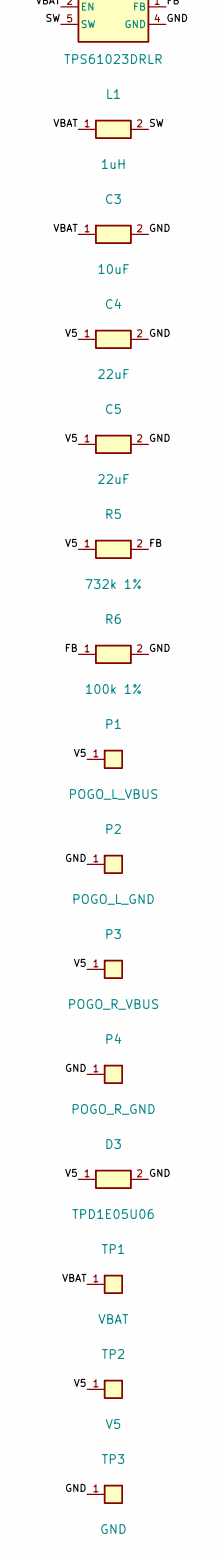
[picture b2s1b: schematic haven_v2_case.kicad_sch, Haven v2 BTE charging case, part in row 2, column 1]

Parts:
C1, C2: 4.7uF; C_0603_1608Metric
C3: 10uF; C_0805_2012Metric
C4, C5: 22uF; C_0805_2012Metric
D1, D3: TPD1E05U06; D_SOD-523; MPN TPD1E05U06DYAR; LCSC C3702980
D2: red; LED_0603_1608Metric
J1: USB-C 16P; USB_C_Receptacle_HRO_TYPE-C-31-M-12; MPN TYPE-C-31-M-12; LCSC C165948
J2: LiPo 1S ~800 mAh; JST_SH_SM02B-SRSS-TB_1x02-1MP_P1.00mm_Horizontal
L1: 1uH; L_1008_2520Metric
P1: POGO_L_VBUS; PogoPin_SMD_D2.0
P2: POGO_L_GND; PogoPin_SMD_D2.0
P3: POGO_R_VBUS; PogoPin_SMD_D2.0
P4: POGO_R_GND; PogoPin_SMD_D2.0
R1, R2: 5.1k; R_0402_1005Metric
R3: 4.02k 1%; R_0402_1005Metric
R4: 1k; R_0402_1005Metric
R5: 732k 1%; R_0402_1005Metric
R6: 100k 1%; R_0402_1005Metric
TP1: VBAT; Pad_1.2
TP2: V5; Pad_1.2
TP3: GND; Pad_1.2
U1: MCP73831T-2ACI/OT; SOT-23-5; MPN MCP73831T-2ACI/OT; LCSC C424093
U2: TPS61023DRLR; SOT-563; MPN TPS61023DRLR; LCSC C1852149

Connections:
/CC1: J1.A5 (CC1), R1.1
/CC2: J1.B5 (CC2), R2.1
/FB: R5.2, R6.1, U2.1 (FB)
/GND: C1.2, C2.2, C3.2, C4.2, C5.2, D1.2 (A), D3.2 (A), J1.A1 (GND), J1.A12 (GND), J1.B1 (GND), J1.B12 (GND), J1.S1 (SHIELD), J2.2 (-), J2.MP, P2.1, P4.1, R1.2, R2.2, R3.2, R6.2, TP3.1, U1.2 (VSS), U2.4 (GND)
/LED_A: D2.1 (A), R4.2
/PROG: R3.1, U1.5 (PROG)
/STAT: D2.2 (K), U1.1 (STAT)
/SW: L1.2, U2.5 (SW)
/V5: C4.1, C5.1, D3.1 (K), P1.1, P3.1, R5.1, TP2.1, U2.6 (VOUT)
/VBAT: C2.1, C3.1, J2.1 (+), L1.1, TP1.1, U1.3 (VBAT), U2.2 (EN), U2.3 (VIN)
/VUSB: C1.1, D1.1 (K), J1.A4 (VBUS), J1.A9 (VBUS), J1.B4 (VBUS), J1.B9 (VBUS), R4.1, U1.4 (VDD)

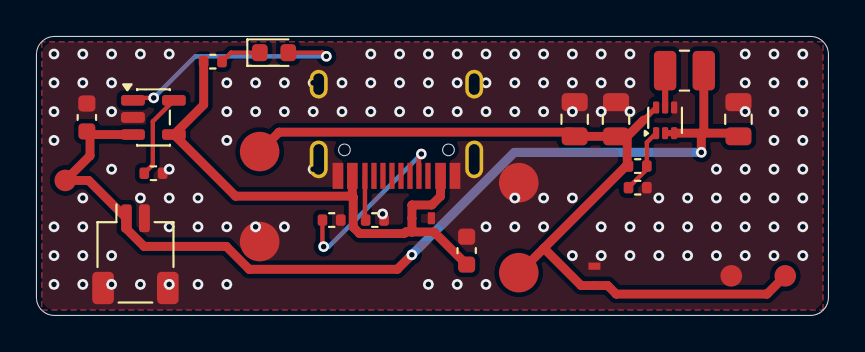
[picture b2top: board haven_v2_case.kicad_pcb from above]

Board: 2 copper layers, 44.0 x 15.5 mm, 26 parts (0 on the bottom side), 11 nets.

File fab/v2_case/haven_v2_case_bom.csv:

Comment,Designator,Footprint,Manufacturer Part,LCSC Part #
4.7uF,"C1,C2",C_0603_1608Metric,CL10A475KO8NNNC,C19666
10uF,C3,C_0805_2012Metric,CL21A106KAYNNNE,C15850
22uF,"C4,C5",C_0805_2012Metric,CL21A226MAQNNNE,C45783
TPD1E05U06,"D1,D3",D_SOD-523,TPD1E05U06DYAR,C3702980
red,D2,LED_0603_1608Metric,KT-0603R,C2286
USB-C 16P,J1,USB_C_Receptacle_HRO_TYPE-C-31-M-12,TYPE-C-31-M-12,C165948
LiPo 1S ~800 mAh,J2,JST_SH_SM02B-SRSS-TB_1x02-1MP_P1.00mm_Horizontal,SM02B-SRSS-TB(LF)(SN),C160402
1uH,L1,L_1008_2520Metric,MPIH252010-1R0M-LF,C490445
5.1k,"R1,R2",R_0402_1005Metric,0402WGF5101TCE,C25905
4.02k 1%,R3,R_0402_1005Metric,CRCW04024K02FKED,C844509
1k,R4,R_0402_1005Metric,0402WGF1001TCE,C11702
732k 1%,R5,R_0402_1005Metric,0402WGF7323TCE,C27016
100k 1%,R6,R_0402_1005Metric,0402WGF1003TCE,C25741
MCP73831T-2ACI/OT,U1,SOT-23-5,MCP73831T-2ACI/OT,C424093
TPS61023DRLR,U2,SOT-563,TPS61023DRLR,C1852149
